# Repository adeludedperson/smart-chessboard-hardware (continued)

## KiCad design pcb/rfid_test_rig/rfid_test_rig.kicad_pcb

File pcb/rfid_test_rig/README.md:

# RFID 2×2 Test Rig

Generated by `generate_rfid_rig.py` from `RIG_PLAN.md`. 80×92mm, 4-layer
(F.Cu / In1.Cu / In2.Cu / B.Cu). Validates RFID antenna coupling + mux
switching for the 64-square chessboard before that board is designed.

## ✅ Build status: DRC CLEAN

```
0 error-severity violations, 0 unconnected items
(kicad-cli pcb drc --severity-error, KiCad 10)
```

Key structural changes made during the final convergence pass (beyond the
original plan):

- **Coils are never x-mirrored** (S2/S4 keep normal winding geometry; only
  the component/port layout mirrors). This puts every hot via on its
  square's east side and eliminates the S1/S2/S4 hot-via pile-up that
  caused the original 3 stubborn crossings. Cold vias still follow the
  layout mirror so the jumper's hot pad faces its via.
- **In1.Cu / In2.Cu are used as strip routing layers** (they only carry
  coil copper inside the squares): SENS3's full strip crossing, S0/S1's
  J1 legs, the U2-VCC 3V3 link, the DVDD spur and LEDD0's J1 leg all ride
  the inner layers, escaping the saturated F/B strip.
- **DEMOD_OUT and SHD are manually routed** (the corridor router ran out of
  row slots in the 86.1–87.3 window; RDY_CLK keeps the pinned 86.3 row).
- **Test points moved**: TP2 (21.6,84.0), TP3 (38.6,83.6), TP4 (40.6,81.9).
- **Zone pad connection is FULL (solid)** — hand-solder rig, kills all
  starved-thermal risk.
- The J1/J2 GND link is registered **before** the corridor/trunk routers so
  they dodge it (fixups placed after them re-collided on every regen).
- Effective DRC clearance is **0.2mm** (not 0.15) — margins were tuned to
  ≥0.2 with the 0.5mm copper-edge rule respected.

Silk-only warnings remain (cosmetic). Verify component rotations in
JLCPCB's viewer before paying, as with every board in this project.

## Zero-solder ordering (nothing hand-assembled)

1. **EM4095 first**: JLCPCB → Parts Manager → Order Parts → *Global Sourcing
   Parts* → search `EM4095HMSO16B+` (Mouser stock). 9–20 business days to
   arrive in their warehouse; the PCBA order can only start after it shows
   "Complete". Loose-part fee ≤ $0.078/pc.
2. **PCBA order**: Standard assembly, SMT + THT in one order (J1/J2 headers
   are wave/hand-soldered by JLC). All other parts are LCSC-stocked per
   BOM.csv — no DNP rows, no TBDs.
3. **S3/S4 tanks are factory-fitted**: 2× 100nF C0G 1206 (C97946) = 200nF →
   8.3 µH resonates at 123.6 kHz, inside the EM4095's 100–150 kHz capture
   range. No post-measurement cap swapping required for bring-up; if the
   measured L differs enough to matter, a cap swap is an optimization, not
   a blocker.
4. Rig connects to any ESP32 devboard with DuPont jumper wires on J1/J2.

## What's implemented (mechanical transcription of RIG_PLAN.md)

- **4 coils**: S1/S2 are stacked 3-layer spirals (In1 18t + In2 18t(mirrored)
  + B 18t, series chain, HOT→In1→In2→B→cold), predicted L≈83µH. S3/S4 are
  B.Cu-only 16t spirals, predicted L≈8.3µH. Mirroring (S2/S4) negates rel-x
  of every coordinate per the plan.
- **Hall (UHE4913G) + WS2812 LED + 0Ω cold jumper** per square, inner-zone
  wiring and F.Cu port crossings (SENS/3V3/5V west or east, GND, LEDD
  DOUT/DIN) exactly per plan geometry.
- **Strip**: EM4095 (U1), 2× 74HC4851 mux (U2/U3), R1/tank/zener clamp
  clusters per antenna, J1 (1×12) / J2 (1×6) headers, 8 test points,
  per-side decoupling.
- **GND zone** on F.Cu only, with 4 keepout squares (half-side 15.4mm) so
  the pour never touches coil territory.

## PLAN-DEVIATION log (local nudges made to pass DRC / avoid physical conflicts)

The plan explicitly authorizes local coordinate nudges where "DRC decides."
Every deviation is also marked with a `# PLAN-DEVIATION:` comment at its
location in `generate_rfid_rig.py`. Summary:

1. **J1/J2 header rotation**: plan says rot270; that runs pins **west** with
   increasing pin number. Used **rot90** instead so pins run **east**
   matching the plan's own pin-list ordering.
2. **+3V3/+5V/SENS/LEDD margin routing**: the plan's single full-board-width
   spine row collides with per-square port verticals and (once coil vias
   were properly registered in the collision system) with coil copper.
   Replaced with fixed-column "vertical trunks" per margin
   (`WCOL`/`ECOL` dicts: west 1.2/2.4/3.6/4.8/6.0mm, east 75.0/76.2/77.4mm,
   plus dedicated far-east SENS2/SENS4 columns 78.2/79.0mm), bridged
   west↔east via the top routing corridor (y<5.5, explicitly coil-free per
   plan) or the inter-row channel (y≈37, also coil-free).
3. **A1/A3 and A2/A4 antenna-drop lanes widened** from the plan's 40.6/37.2
   and 73.6/68.5 to 41.1/36.7 and 74.1/68.0 — at the plan's spacing the
   tank-cap clusters of adjacent antennas were only 0.8mm apart (footprints
   physically overlapping).
4. **Tank-cap/zener offset from lane center** tightened from the plan's
   1.3mm to 0.8mm for the same reason (adjacent-cluster spacing).
5. **S2's coil hot via / S4's coil hot via** shortened (stub magnitude
   16.1/16.2 → 14.0/14.6mm) — the plan's symmetric stub length put S1's and
   S2's (and S3's and S4's) hot vias only 0.6-0.8mm apart in the shared
   inter-column gap.
6. **A<n> test points** (TP5-TP8) relocated from the plan-implied feed-line
   position onto each antenna's own vertical run, off the AM<n> zener
   midpoint stitch and off J1's pin7 THT column, to avoid clearance
   violations with unrelated nets/pads.
7. **E5VY / channel-crossing rows** for the LEDD2 corridor (S1↔S2, inter-row
   channel) tuned to a ~0.3mm-wide safe window between S1's DIN port via
   (needs 0.9mm clearance) and S3's own outermost coil turn (invisible to
   the generic router since it isn't axis-aligned) — the single tightest
   spot on the board.

## Known generator bugs fixed during bring-up (documented for future reuse)

- `led_dout/gnd/din/vdd` port-crossing coordinates were double-counting the
  LED footprint's own +3.9mm y-offset (the plan's pad offsets are already
  relative to the *square* center, matching the `wantL` pad-matching dict).
  This misaligned every LED port stub by exactly 3.9mm and was the single
  largest cause of "unconnected" DRC items (fixed → unconnected 57→37).
- `vertical_trunk()`'s per-point `hseg()` call discarded the jogged y and
  placed the via at the *original* requested y — if the exact row was
  blocked and `hseg` jogged elsewhere, the via missed the actual track
  entirely. Fixed by capturing and using `hseg`'s return value (unconnected
  37→28, 3 shorting_items→0).
- `coil` hot/cold vias were created with `via_at()` (a separate helper from
  the general router's `rvia()`) and were invisible to the collision
  registry — later routing could (and did) route straight through them.
  Fixed by having `via_at()`/`seg()` register into the same `segs`/`via_pts`
  tables the router already consults.

## Predicted electrical values (from RIG_PLAN.md §2/3, Wheeler approximation)

| Square | Construction | Predicted L | Tank cap | Predicted resonance |
|---|---|---|---|---|
| S1, S2 | In1(18t)+In2(18t)+B(18t) stacked, series, 54 turns total | ≈83 µH | 2× 10 nF (parallel, per side) → 20nF net… fit to measured L | target 125kHz — **refit after measuring L**, provisional tank ≈19.6 nF |
| S3, S4 | B.Cu only, 16 turns | ≈8.3 µH | 2× 100 nF | provisional tank ≈195 nF, **refit after measuring L** |

Both candidates predict V_ANT(peak) far below the 69V worst case in
DESIGN_V3_RFID.md (≈8V at 83µH) — the zener clamps (D<n>a/D<n>b, 15V SOD-523)
are belt-and-braces, not required for survival at these inductances.

## EM4095 pinout: VERIFIED against the official EM Microelectronic datasheet (SO16, 2026-09-01) — matches the board pin-for-pin. This generator ties ANT2/MOD/VSS/DVSS to GND directly
(single-ended antenna drive, coil cold legs grounded) — **the plan's pinout
was transcribed as given and not independently re-verified against an EM4095
datasheet PDF in this pass.** Do this before ordering.

## Bring-up procedure

1. **Visual inspection** — check silkscreen ref-des against BOM, confirm no
   solder bridges on the tight tank/zener clusters (courtyard warnings above
   mean these pads are closer together than ideal; hand-solder carefully or
   have the assembly house double-check paste stencil apertures there).
2. **Power-up dry test** — before installing U1/U2/U3, apply +5V/+3V3/GND
   only via J1, confirm no shorts (should draw µA, not amps).
3. **Hall + LED test** — populate U_S<n>H (hall) and D_S<n> (LED) only.
   3.3V/5V present, no RFID field: LED should be addressable via LEDD0 chain
   (J1 pin7 → S3 → S1 → S2 → S4). Hall SENS<n> outputs should read a fixed
   logic level (idle) via J2.
4. **Antenna resonance check** — before installing U1 (EM4095), measure each
   coil's inductance directly at its cold-jumper pads (remove jumper,
   measure across A<n>↔GND at the coil side) with an LCR meter. Compare to
   predicted 83µH (S1/S2) / 8.3µH (S3/S4). **Refit tank cap value** to hit
   125kHz resonance: C = 1/((2π·125kHz)² · L_measured).
5. **Full RFID test** — populate U1, U2, U3. Select antenna via
   S0/S1 + EN0/EN1 (J1 pins 8,9,10,11), present a 125kHz tag, scope
   RDY_CLK/DEMOD_OUT (J1 pins 4,6) and the per-antenna A<n> test points
   (TP5-TP8) for carrier amplitude — should read ≈8V pk on the 83µH
   antennas per predicted V_ANT.
6. **Cross-talk check** — with a tag over S1, confirm S2/S3/S4 (unselected)
   don't false-trigger; this is the whole point of the 2×2 rig before
   committing to a 64-square mux tree.

## Cost estimate

~₹1.5k for this rig (per plan): EM4095 (~₹150), 2× 74HC4851 (~₹80 ea),
4× UHE4913G hall (~₹40 ea), 4× WS2812C-2020 (~₹30 ea), passives/connectors
(~₹300), 10× 125kHz RFID tags for testing (~₹400), PCB fab (~₹300-500 for
a 4-layer 80×92mm prototype run).

## Files

- `generate_rfid_rig.py` — the generator (run with KiCad's bundled Python 3.9)
- `rfid_test_rig.kicad_pcb` — output board (see DRC status above)
- `gerbers/` — F/In1/In2/B copper, mask, paste, silkscreen, edge cuts, drill
- `BOM.csv`, `positions.csv` — JLCPCB-style assembly files (LCSC part
  numbers filled where known; zener/EM4095/C0G cap LCSC #s marked
  `TBD-verify` — pick real parts before ordering assembly)

## BOM notes

- 74HC4851PW = C458225, WS2812C-2020 = C2976072, UHE4913G = C86815,
  100nF 0603 = C5137636 (from plan).
- EM4095 (SOIC-16), 15V SOD-523 zeners, and the C0G tank/decoupling caps are
  marked `TBD-verify` in BOM.csv — plan flagged these as needing a real
  LCSC part number pick before ordering; not resolved in this pass.

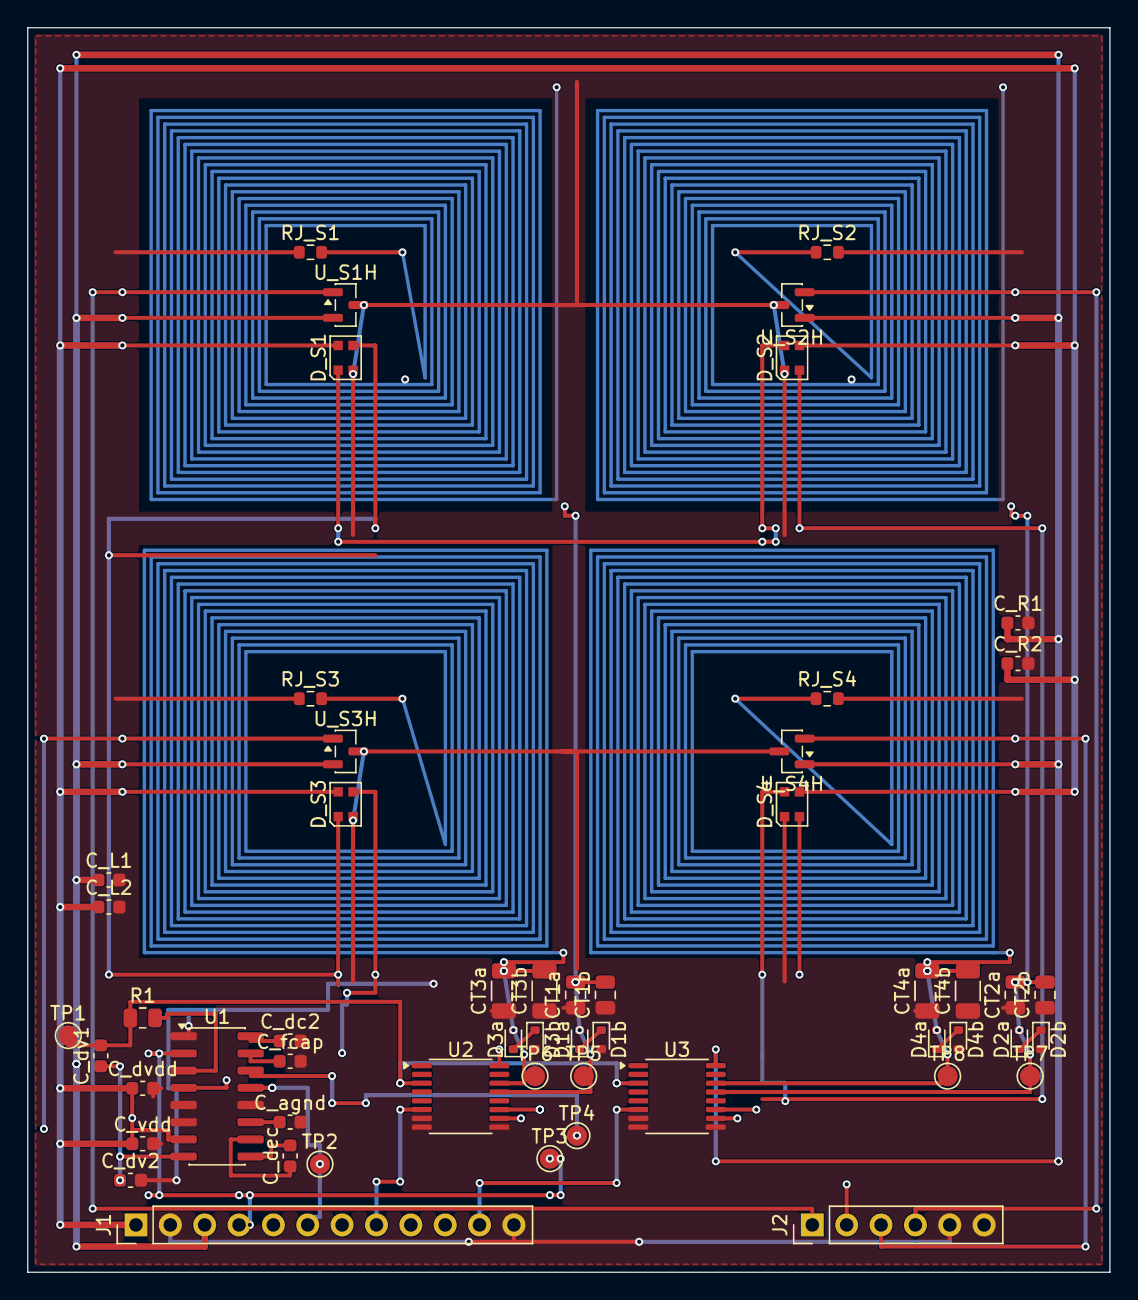
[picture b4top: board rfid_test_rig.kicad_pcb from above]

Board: 4 copper layers, 80.0 x 92.0 mm, 54 parts (0 on the bottom side), 34 nets.

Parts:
CT1a, CT1b, CT2a, CT2b: 10n; C_0805_2012Metric
CT3a, CT3b, CT4a, CT4b: 100n_1206; C_1206_3216Metric
C_L1, C_L2: 100nF; C_0603_1608Metric
C_R1, C_R2: 100nF; C_0603_1608Metric
C_agnd: 220nF; C_0603_1608Metric
C_dc2: 10n_0603; C_0603_1608Metric
C_dec: 100nF; C_0603_1608Metric
C_dv1: 47pF; C_0603_1608Metric
C_dv2: 1.5nF; C_0603_1608Metric
C_dvdd: 100nF; C_0603_1608Metric
C_fcap: 10nF; C_0603_1608Metric
C_vdd: 100nF; C_0603_1608Metric
D1a, D1b, D2a, D2b, D3a, D3b, D4a, D4b: 15V_SOD523; D_SOD-523
D_S1, D_S2, D_S3, D_S4: WS2812C-2020; LED_WS2812B-2020_PLCC4_2.0x2.0mm
J1: IN; PinHeader_1x12_P2.54mm_Vertical
J2: OUT; PinHeader_1x06_P2.54mm_Vertical
R1: 33R; R_0805_2012Metric
RJ_S1, RJ_S2, RJ_S3, RJ_S4: 0R; R_0603_1608Metric
TP1, TP2, TP3, TP4, TP5, TP6, TP7, TP8: TP; TestPoint_Pad_D1.5mm
U1: EM4095; SOIC-16_3.9x9.9mm_P1.27mm
U2, U3: 74HC4851PW; TSSOP-16_4.4x5mm_P0.65mm
U_S1H, U_S2H, U_S3H, U_S4H: UHE4913G; SOT-23

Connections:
+3V3: C_L1.1, C_R1.1, J1.3, U2.16, U3.16, U_S1H.2, U_S2H.1, U_S3H.2, U_S4H.1
+5V: C_L2.1, C_R2.1, C_dvdd.1, C_vdd.1, D_S1.4, D_S2.3, D_S3.4, D_S4.3, J1.1, U1.4, U1.7
A1: CT1a.2, CT1b.2, D1a.2, RJ_S1.2, TP5.1, U2.13
A2: CT2a.2, CT2b.2, D2a.2, RJ_S2.1, TP7.1, U3.13
A3: CT3a.2, CT3b.2, D3a.2, RJ_S3.2, TP6.1, U2.14
A4: CT4a.2, CT4b.2, D4a.2, RJ_S4.1, TP8.1, U3.14
AGND_N: C_agnd.1, U1.11
AM1: D1a.1, D1b.1
AM2: D2a.1, D2b.1
AM3: D3a.1, D3b.1
AM4: D4a.1, D4b.1
ANT1: R1.2, U1.3
ANT_DRV: C_dv1.2, R1.1, TP1.1, U2.3, U3.3
CDECI: C_dec.1, U1.10
CDECO: C_dec.2, U1.9
DC2: C_dc2.1, U1.16
DEMOD_IN: C_dv1.1, C_dv2.1, U1.8
DEMOD_OUT: J1.6, TP2.1, U1.13
EN0: J1.8, U2.6
EN1: J1.11, U3.6
FCAP: C_fcap.1, U1.15
GND: CT1a.1, CT1b.1, CT2a.1, CT2b.1, CT3a.1, CT3b.1, CT4a.1, CT4b.1, C_L1.2, C_L2.2, C_R1.2, C_R2.2, C_agnd.2, C_dc2.2, C_dv2.2, C_dvdd.2, C_fcap.2, C_vdd.2, D1b.2, D2b.2, D3b.2, D4b.2, D_S1.2, D_S2.1, D_S3.2, D_S4.1, J1.2, J1.12, J2.5, J2.6, RJ_S1.1, RJ_S2.2, RJ_S3.1, RJ_S4.2, U1.1, U1.5, U1.6, U1.12, U2.7, U2.8, U2.9, U3.7, U3.8, U3.9, U_S1H.3, U_S2H.3, U_S3H.3, U_S4H.3
LEDD0: D_S3.3, J1.7
LEDD1: D_S1.3, D_S3.1
LEDD2: D_S1.1, D_S2.4
LEDD3: D_S2.2, D_S4.4
RDY_CLK: J1.4, TP3.1, U1.2
S0: J1.9, U2.11, U3.11
S1: J1.10, U2.10, U3.10
SENS1: J2.1, U_S1H.1
SENS2: J2.4, U_S2H.2
SENS3: J2.2, U_S3H.1
SENS4: J2.3, U_S4H.2
SHD: J1.5, TP4.1, U1.14

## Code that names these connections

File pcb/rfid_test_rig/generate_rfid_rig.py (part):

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# --- U1 EM4095 SOIC-16 @ (14,79) rot0
U1X, U1Y = 14.0, 79.0
u1 = place(fp("Package_SO", "SOIC-16_3.9x9.9mm_P1.27mm"), "U1", U1X, U1Y, rot=0, value="EM4095")
U1PIN = {1:"GND",2:"RDY_CLK",3:"ANT1",4:"+5V",5:"GND",6:"GND",7:"+5V",8:"DEMOD_IN",
         9:"CDECO",10:"CDECI",11:"AGND_N",12:"GND",13:"DEMOD_OUT",14:"SHD",15:"FCAP",16:"DC2"}
for nm in ("ANT1","CDECO","CDECI","AGND_N","FCAP","DC2"): net(nm)
assign(u1, {str(k): v for k,v in U1PIN.items()})
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r1.SetValue("33R")
r1p = place_by_pos(r1, "R1", 8.5, 73.2, {"W": (-1.0,0.0), "E": (1.0,0.0)}, rot0=0)
assign(r1, {r1p["W"]: "ANT_DRV", r1p["E"]: "ANT1"})
# R1 pad2(ANT1) -> U1 pin3(ANT1): route north then east, west of U1's body.
_r1e = pad_xy(r1, r1p["E"]); _u1p3 = pad_xy(u1, "3")
# DRC-FIX: the old route's vertical at x=9.41 walled off U1 pin2's west
# escape (RDY_CLK). Go east over the body, down the pad-column gap (x=13.9,
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cdv2 = fp("Capacitor_SMD", "C_0603_1608Metric"); cdv2.SetValue("1.5nF")
cdv2p = place_by_pos(cdv2, "C_dv2", 7.6, 85.2, {"W": (-0.8,0.0), "E": (0.8,0.0)}, rot0=0)
assign(cdv2, {cdv2p["W"]: "DEMOD_IN", cdv2p["E"]: "GND"})
# DEMOD_IN chain: cdv1.S -> cdv2.W -> U1 pin8 (net-assigned above but never
# actually wired with copper).
# Routed on B.Cu at cdv2's own x (6.83, clear of the SENS1 west-margin
# column at 4.8) via the router, so later crossings auto-avoid it.
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vseg(_dv2w[1], _u1p8[1], _dicol, "DEMOD_IN")
seg(0, 0, _dicol, _u1p8[1], _u1p8[0], _u1p8[1], "DEMOD_IN", LF, TRK_SIG)

# --- C_dec 100nF r90 @ (19.4,83.4): bridges pin9(CDECO)/pin10(CDECI)
cdec = fp("Capacitor_SMD", "C_0603_1608Metric"); cdec.SetValue("100nF")
cdecp = place_by_pos(cdec, "C_dec", 19.4, 83.4, {"N": (0.0,-0.8), "S": (0.0,0.8)}, rot0=90)
assign(cdec, {cdecp["N"]: "CDECO", cdecp["S"]: "CDECI"})

# --- C_agnd 220nF rot0 @ (19.4,80.9): pad1->AGND_N(pin11), pad2->GND
cagnd = fp("Capacitor_SMD", "C_0603_1608Metric"); cagnd.SetValue("220nF")
cagndp = place_by_pos(cagnd, "C_agnd", 19.4, 80.9, {"W": (-0.8,0.0), "E": (0.8,0.0)}, rot0=0)
assign(cagnd, {cagndp["W"]: "AGND_N", cagndp["E"]: "GND"})
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cdc2p = place_by_pos(cdc2, "C_dc2", 19.4, 74.9, {"W": (-0.8,0.0), "E": (0.8,0.0)}, rot0=0)
assign(cdc2, {cdc2p["W"]: "DC2", cdc2p["E"]: "GND"})

# --- C_fcap 10nF rot0 @ (19.4,76.4): pad1->pin15(FCAP), pad2 GND
cfcap = fp("Capacitor_SMD", "C_0603_1608Metric"); cfcap.SetValue("10nF")
cfcapp = place_by_pos(cfcap, "C_fcap", 19.4, 76.4, {"W": (-0.8,0.0), "E": (0.8,0.0)}, rot0=0)
assign(cfcap, {cfcapp["W"]: "FCAP", cfcapp["E"]: "GND"})
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seg(0, 0, _cdecn[0], _cdecn[1], 18.0, _cdecn[1], "CDECO", LF, TRK_SIG)
seg(0, 0, 18.0, _cdecn[1], 18.0, _u1p9[1], "CDECO", LF, TRK_SIG)
seg(0, 0, 18.0, _u1p9[1], _u1p9[0], _u1p9[1], "CDECO", LF, TRK_SIG)
# CDECI (S pad, y=84.2) targets pin10 (y=82.175) which is ABOVE it -- a
# direct path crosses right through CDECO's own N->pin9 route at x=19.4.
# Detour further south and around instead. DRC-FIX tracks_crossing: the old
# detour column (18.5) sat inside CDECO's new horizontal span [18.0,19.4] at
# y=83.445 -- move the detour column to 15.0 (west of pin9/10's own x=16.475
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j1 = fp("Connector_PinHeader_2.54mm", "PinHeader_1x12_P2.54mm_Vertical")
j1.SetReference("J1"); j1.SetValue("IN"); board.Add(j1)
j1.SetPosition(VECTOR2I(MM(8.0), MM(88.5))); j1.SetOrientationDegrees(90)
J1PIN = {1:"+5V",2:"GND",3:"+3V3",4:"RDY_CLK",5:"SHD",6:"DEMOD_OUT",7:"LEDD0",
         8:"EN0",9:"S0",10:"S1",11:"EN1",12:"GND"}
assign(j1, {str(k): v for k,v in J1PIN.items()})

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j2 = fp("Connector_PinHeader_2.54mm", "PinHeader_1x06_P2.54mm_Vertical")
j2.SetReference("J2"); j2.SetValue("OUT"); board.Add(j2)
j2.SetPosition(VECTOR2I(MM(58.0), MM(88.5))); j2.SetOrientationDegrees(90)
J2PIN = {1:"SENS1",2:"SENS3",3:"SENS4",4:"SENS2",5:"GND",6:"GND"}
assign(j2, {str(k): v for k,v in J2PIN.items()})
# DRC-FIX starved_thermal: J2 pin5 GND had only 1 zone spoke connected as a
# bare THT pad -- short stub south into open pour gives it a second spoke.
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# centre y): cvdd centre 82.5 -> safe_y=81.5 (1.0mm clear); cdvdd centre
# 78.4 -> safe_y=77.3 (1.1mm clear, pin4 sits almost on top of the cap).
cap_to_pin(cvdd, cvddp, "7", safe_y=81.5)
# DRC-FIX clearance: pin4's own neighbours (pin3 ANT1 above, pin5 GND
# below) plus the cap's own GND pad sit in one continuous forbidden band
# (76.4..80.3) with no safe crossing height. pin4 and pin7 are both +5V
# already (same net) -- route to pin7's safe spot instead; electrically
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# --- W/E port vias -> strip. West squares (S1,S3) exit at cx-16.5 (west margin);
# east squares (S2,S4) exit at cx+16.5 (east margin, mirrored).
SENSPORT = {"S1":"SENS1","S2":"SENS2","S3":"SENS3","S4":"SENS4"}
J2PIN_OF_SENS = {"SENS1":"1","SENS3":"2","SENS4":"3","SENS2":"4"}
j2sens_y = {"SENS1": 85.9, "SENS3": 86.4, "SENS4": 86.9, "SENS2": 87.3}
# SENS1/SENS3 use the west margin trunk columns; SENS2/SENS4 use dedicated
# far-east columns (78.6/79.4, past the +3V3/+5V/LEDD3 trunk at 75.0-77.4 and
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# there to J2 pin2 with the general-purpose router (F.Cu jog + B.Cu drop),
# same as the hot-via-to-cluster routes use.
_s3_pv = inner["S3"][6]["W_SENS"]
_s3_j2 = pad_xy(j2, J2PIN_OF_SENS["SENS3"])
# TOPOLOGY-FIX (root cause of the last tracks_crossing): long_route's B.Cu
# descent at x=60.54 ran straight through S4's B-only coil turns and its
# cold-via diagonal -- coil copper is deliberately NOT in the collision
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# x 55.5-73) or the strip's F lanes, while any B descent x>8 hits the +5V B
# feeder wall at y=69.7. Only clean corridor: the plan's own west-margin
# column (WCOL['SENS3']=1.2, west of the feeder's x=8.0 start), approaching
# J2 pin2 from the SOUTH (y=90.6 lane) like SENS2/SENS4 do, clear of
# SENS1's x=58 descent.
seg(0, 0, _s3_pv[0], _s3_pv[1], WCOL["SENS3"], _s3_pv[1], "SENS3", LF, TRK_SIG)
rvia(WCOL["SENS3"], _s3_pv[1], "SENS3")
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# that grazed pin3's pad -- straight west only.
u1_rdy  = escape(u1, "2",  [W_], dist=2.6)
u1_demo = escape(u1, "13", [E])
# pin14 sits between the CDC2/FCAP decoupling caps at x=19.4 -- dogleg south
# first (clear of both the pin13 stub at y=78.36 and the caps) then east.
# straight-down at p14x would run through pin13's pad (same x column,
# y=78.365, directly between pin14 and the y=79.5 turn) -- nudge east 1.0mm
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seg(0, 0, u2_z[0], u2_z[1], u2_z[0], 76.55, "ANT_DRV", pcbnew.B_Cu, TRK_SIG)
seg(0, 0, u2_z[0], 76.55, u3_z[0], 76.55, "ANT_DRV", pcbnew.B_Cu, TRK_SIG)
seg(0, 0, u3_z[0], 76.55, u3_z[0], u3_z[1], "ANT_DRV", pcbnew.B_Cu, TRK_SIG)
# Bypass R1's own ANT1 pad (east of r1w, same row) by dropping to a clear
# row first, then traverse the whole width (still above U1's 74.555 pad
# block) before dropping straight down to u2_z.
seg(0, 0, r1w[0], r1w[1], r1w[0], ANT_BYPASS_Y, "ANT_DRV", LF, TRK_SIG)
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seg(0, 0, 25.0, 79.5, 25.0, 78.9, "SHD", pcbnew.B_Cu, TRK_SIG)
seg(0, 0, 25.0, 78.9, 40.6, 78.9, "SHD", pcbnew.B_Cu, TRK_SIG)
seg(0, 0, 40.6, 78.9, 40.6, 81.9, "SHD", pcbnew.B_Cu, TRK_SIG)
# DEMOD_OUT: manual B.Cu route pin13-escape -> TP2 -> J1 pad6 (no corridor
# slot left; B.Cu is empty along this path).
_dm = u1_demo
rvia(_dm[0], _dm[1], "DEMOD_OUT")
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    rvia(xcol, yb, nm)
    drop(xcol, ya, yb, nm, jogs=mjogs)

# LEDD0: J1.pin7 (y=88.5) -> S3.S_DIN port via (y=70.0) -- both already below
# S3's coil radius (68.4), so a plain corridor works with no margin detour.
# S3.S_DIN's own column (x=25.7) sits within 0.9mm of EN0's already-routed
# vias (25.78/25.94 @ y=84.5), and the generic corridor() couldn't find a
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# SHD: bridge the missing vseg piece; via where the F run starts; via on TP4
seg(0, 0, 22.5, 77.495, 22.5, 79.5, "SHD", BC, TRK_SIG); rvia(22.5, 79.5, "SHD")
rvia(40.6, 81.9, "SHD")
# RDY_CLK: via on TP3 (escape now handles the pin2 stub itself)
rvia(38.6, 83.6, "RDY_CLK")
# GND: U1 pin1 + C_dvdd GND pad are pour-orphans (ANT1/RDY tracks fence
# them). Tie both to the strip-top pour through a small B.Cu network.
seg(0, 0, 11.9, 74.5, 11.9, 73.8, "GND", LF, TRK_SIG)   # pin1 pad exit north
rvia(11.9, 73.8, "GND")
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seg(0, 0, 72.425, 47.0, 72.425, 48.2, "+5V", LF, TRK_SIG)
# +5V: DVDD (U1 pin4) spur -- C_dvdd's GND stub blocks the direct west
# approach, so run north of pin3's pad, down the free half of the U1
# pad-column gap (x=15.1; ANT1 owns 13.9 but its vertical ends at pin3's
# row), and back west into pin4.
# west F approaches are all fenced (C_dvdd, its GND stub, pin3's pad) --
# escape east through the pad-column gap, then In2 back to the +5V riser.
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
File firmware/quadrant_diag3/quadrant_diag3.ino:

// quadrant_diag3 - hold PL LOW (transparent load). SER_OUT then mirrors S15 live.
// No clocking involved at all - pure sensor test.
const int PIN_PL=25, PIN_CP=26, PIN_SER_OUT=27, PIN_SER_IN=14;
int last=-1; unsigned long changes=0;
void setup(){
  Serial.begin(115200); delay(400);
  pinMode(PIN_PL,OUTPUT); pinMode(PIN_CP,OUTPUT);
  pinMode(PIN_SER_IN,OUTPUT); pinMode(PIN_SER_OUT,INPUT);
  digitalWrite(PIN_PL,LOW);      // transparent: Q7 follows D7 = SENS_15
  digitalWrite(PIN_CP,LOW);
  digitalWrite(PIN_SER_IN,LOW);
  Serial.println("\n\n=== LIVE S15 SENSOR WATCH ===");
  Serial.println("PL held LOW -> output follows S15 directly, no clock needed.");
  Serial.println("Put the magnet on S15. Try BOTH faces of the magnet.\n");
}
void loop(){
  int v=digitalRead(PIN_SER_OUT);
  if(v!=last){ changes++; last=v;
    Serial.printf("S15 = %s      (changes so far: %lu)\n", v? "EMPTY (high)":"*** MAGNET *** (low)", changes); }
  delay(30);
}
